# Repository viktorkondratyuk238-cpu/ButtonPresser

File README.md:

# ButtonPresser
Its a musical thingy
and its super cool, and it will never see the real world but ill make it in KiCAD and even an enclosure, and it will be super cool and super working yes! in all seriousnes it has 5 buttons, a normal ESP32 and a buzzer when you press a button it makes a differently pitcehd sound. m making the PCB in kicad and enclosre in Fusion.

Its powered with a simple 1S LiPo, charging it is on you it doesnt have a charging circuit.

as for flashing the ESP to make it as simple as possible i decided that flashing it would officialy be a 2 to 3 man operation. the flashing will need 3 wires, so you just hold some jumpers on the board plugged into a UART like a CH340 and hope your hand doesnt slip. here is the step by step aswell as where each wire goes. 

Make sure SW6 is on and the battery is unplugged.
Press and hold SW4 (IO9). That’s the boot button.
While holding SW4, plug the battery into J1. The chip starts in download mode.
Release SW4.
Click Upload in the IDE
Unplug the battery and the adapter, then plug the battery back in. The new code runs.

Wire|	PCB end      |CH340 end                                                                                                                                                                                                   
1	  |GND	U1 pin 9 |(GND)                                                                                                                                                                                                       
2	  |RX	U1 pin 12  |(IO21/TXD)                                                                                                                                                                                                  
3	  |TX	U1 pin 11  |(IO20/RXD)                                                                                                                                                                                                  

and here is the picture in Fusion  ik the image looks bad like its clipping through, trust me it doesnt tho (atelast think it doesnt)

BOM:
the PCB
3d enclosure
301030 LiPo
CH340
Jumpers

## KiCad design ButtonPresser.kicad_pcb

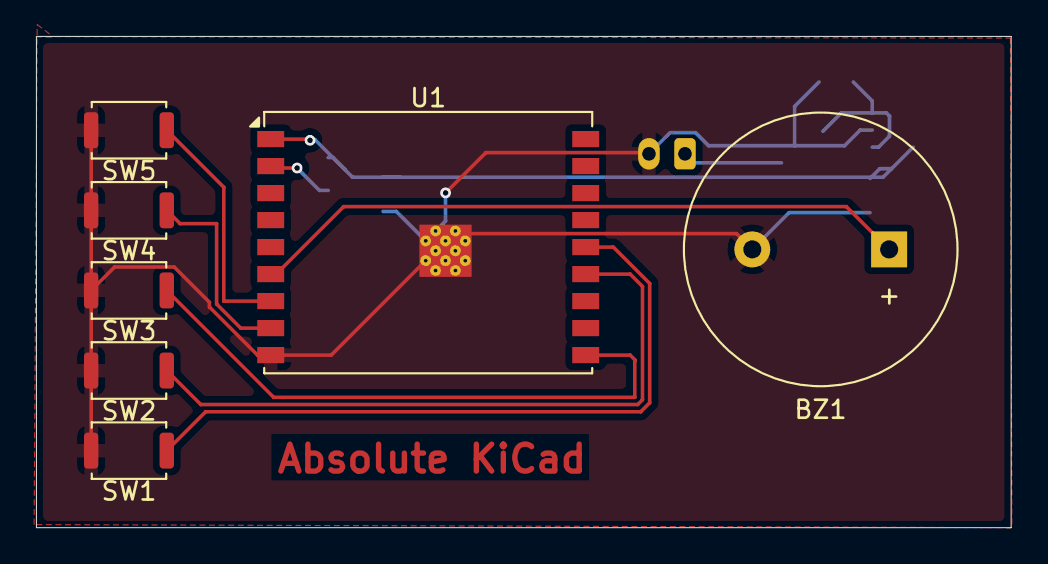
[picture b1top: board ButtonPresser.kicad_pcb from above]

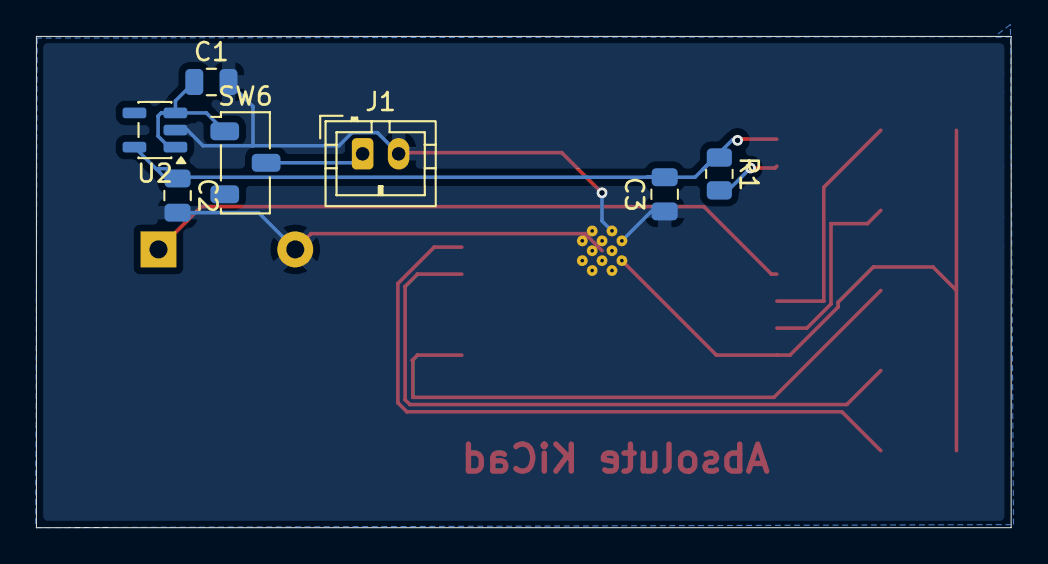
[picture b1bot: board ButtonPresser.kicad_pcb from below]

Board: 2 copper layers, 54.2 x 27.3 mm, 14 parts (7 on the bottom side), 11 nets.

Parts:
BZ1: Buzzer; Buzzer_15x7.5RM7.6
C1, C2: 10 µF; C_0805_2012Metric
C3: 0,1 µF; C_0805_2012Metric
J1: Conn_01x02; JST_PH_B2B-PH-K_1x02_P2.00mm_Vertical
R1: 10 kΩ; R_0805_2012Metric
SW1, SW2, SW3, SW4, SW5: SW_Push; SW_Push_SPST_NO_Alps_SKRK
SW6: SW_SPDT; Nidec_Copal_CAS-120A
U1: ESP32-C3-WROOM-02U
U2: AP2112K-3.3; SOT-23-5

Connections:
unnamed: BZ1.1 (+), U1.6 (IO7)
unnamed: BZ1.2 (-), C1.2, C2.2, C3.1, J1.2, SW1.2, SW2.2, SW3.2, SW4.2, SW5.2, U1.9 (GND), U1.19 (GND), U2.2 (GND)
unnamed: J1.1, SW6.2 (B)
unnamed: C1.1, SW6.1 (A), U2.1 (VIN), U2.3 (EN)
unnamed: C2.1, C3.2, R1.1, U1.1 (3V3), U2.5 (VOUT)
unnamed: R1.2, U1.2 (EN)
unnamed: SW5.1, U1.7 (IO8)
unnamed: SW4.1, U1.8 (IO9)
unnamed: SW3.1, U1.10 (IO10)
unnamed: SW2.1, U1.13 (IO18)
unnamed: SW1.1, U1.14 (IO19)
